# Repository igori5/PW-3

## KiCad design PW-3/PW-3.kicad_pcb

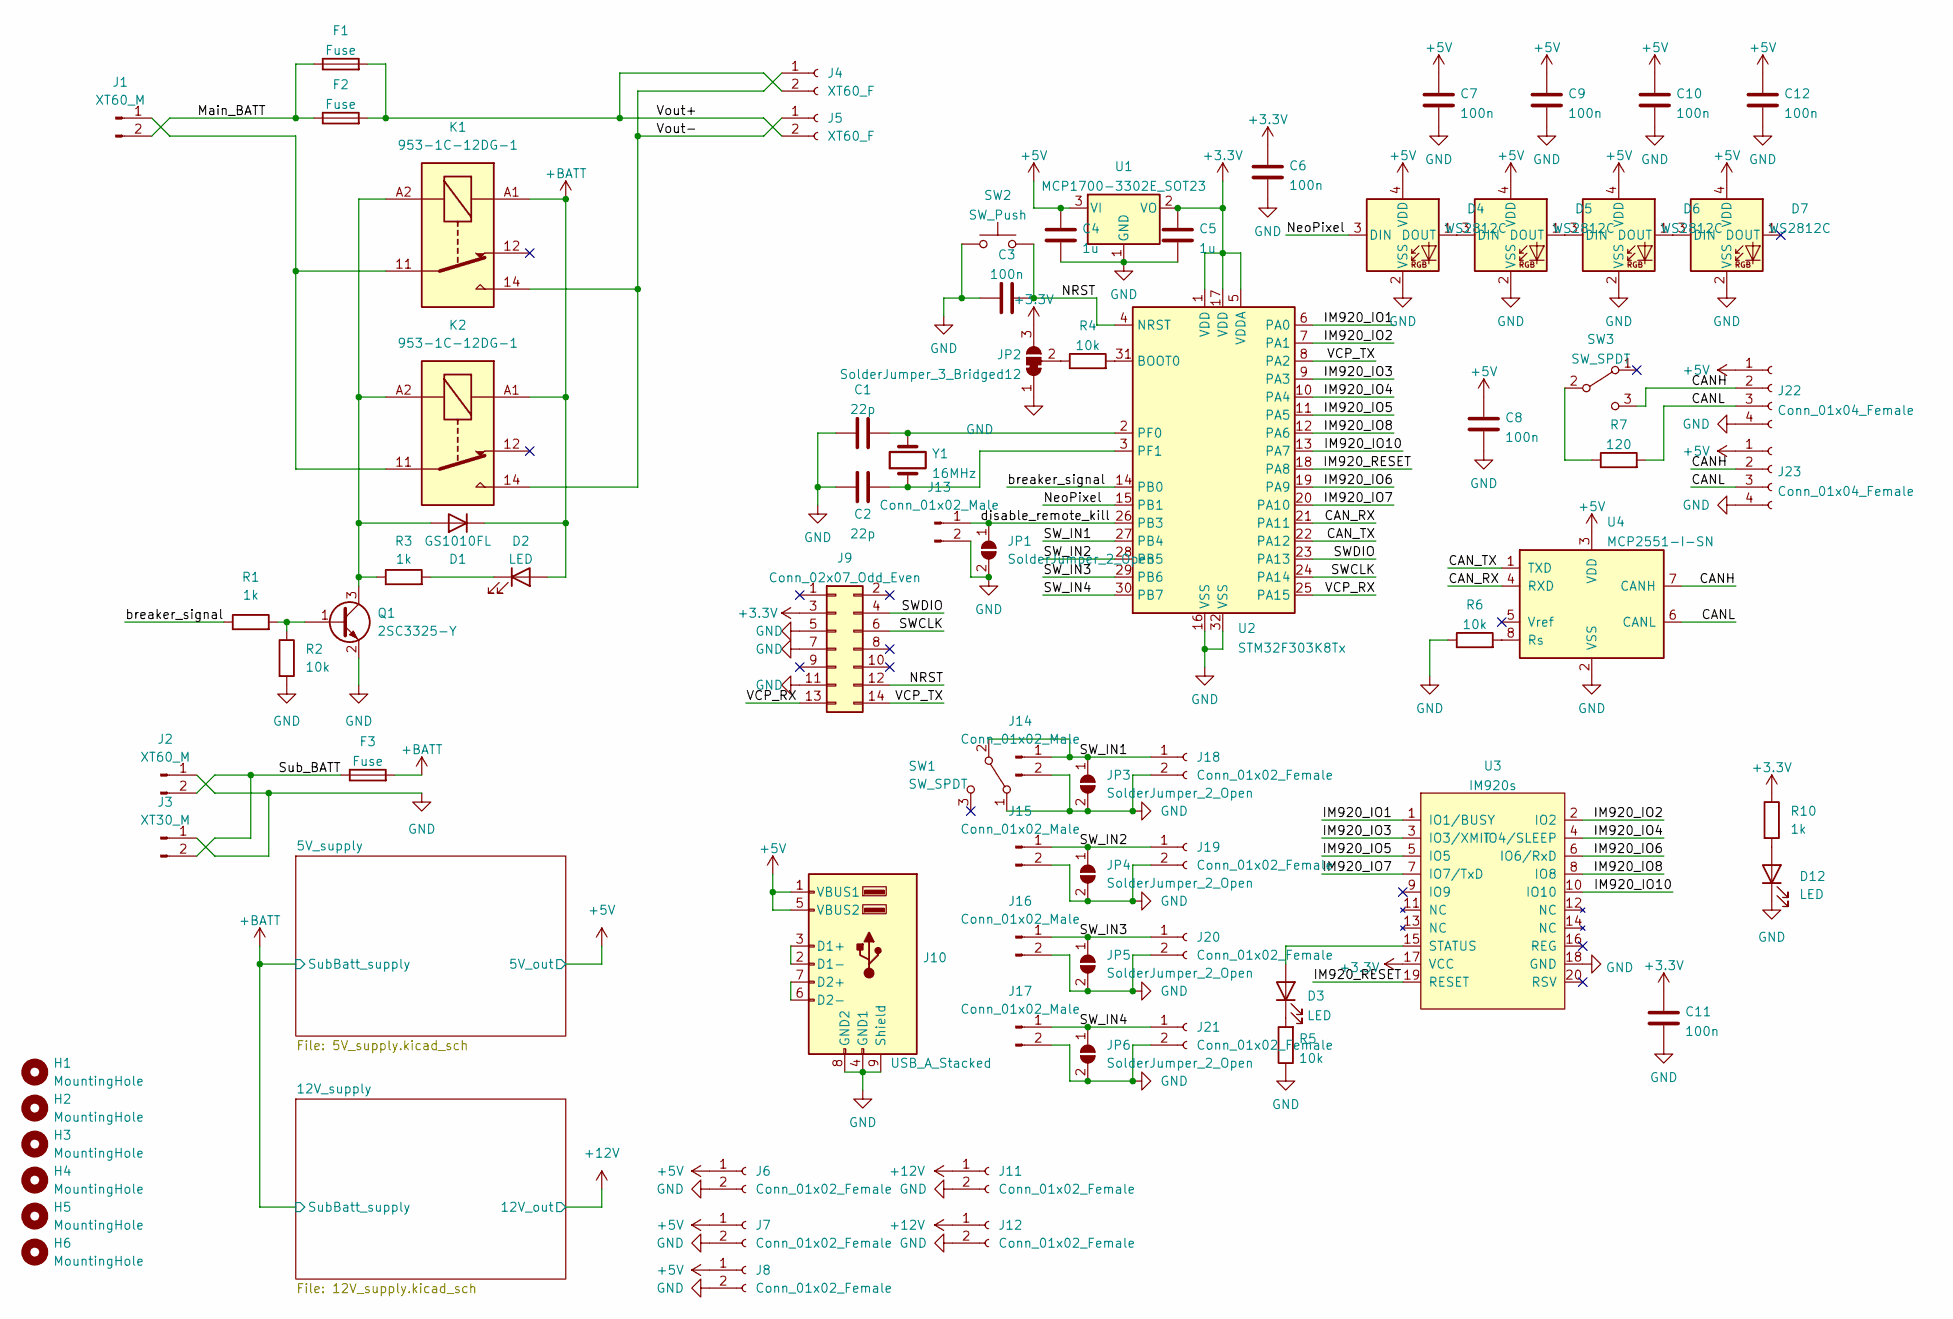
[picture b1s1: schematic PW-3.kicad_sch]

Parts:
C1, C2: 22p; C_0603_1608Metric
C3, C6, C7, C8, C9, C10, C11, C12: 100n; C_0603_1608Metric
C4, C5: 1u; C_0603_1608Metric
D1: GS1010FL; D_SOD-123
D2, D3, D12: LED; LED_0603_1608Metric
D4, D5, D6, D7: WS2812C; LED_2020Metric_WS2812C_2.0x2.0mm_P1.0mm
F1, F2, F3: Fuse; Fuseholder_Keystone_3568
H1, H2, H3, H4, H5, H6: MountingHole; MountingHole_3.2mm_M3_Pad_Via
J1, J2: XT60_M; AMASS_XT60PW-M_1x02_P7.20mm_Horizontal
J3: XT30_M; AMASS_XT30PW-M_1x02_P2.50mm_Horizontal
J4, J5: XT60_F; AMASS_XT60PW-F_1x02_P7.20mm_Horizontal
J6, J7, J8, J11, J12, J18, J19, J20, J21: Conn_01x02_Female; JST_XA_S02B-XASK-1_1x02_P2.50mm_Horizontal
J9: Conn_02x07_Odd_Even; PinHeader_2x07_P1.27mm_Vertical_SMD
J10: USB_A_Stacked; USB_A_Wuerth_61400826021_Horizontal_Stacked
J13, J14, J15, J16, J17: Conn_01x02_Male; PinHeader_1x02_P2.54mm_Vertical
J22, J23: Conn_01x04_Female; JST_XA_S04B-XASK-1_1x04_P2.50mm_Horizontal
JP1, JP3, JP4, JP5, JP6: SolderJumper_2_Open; SolderJumper-2_P1.3mm_Open_RoundedPad1.0x1.5mm
JP2: SolderJumper_3_Bridged12; SolderJumper-3_P1.3mm_Bridged12_RoundedPad1.0x1.5mm
K1, K2: 953-1C-12DG-1; Relay_SPDT_RAYEX-L90S
Q1: 2SC3325-Y; SOT-23
R1, R3, R10: 1k; R_0603_1608Metric
R2, R4, R5, R6: 10k; R_0603_1608Metric
R7: 120; R_0603_1608Metric
SW1, SW3: SW_SPDT; PinHeader_1x03_P2.54mm_Vertical
SW2: SW_Push; TVAF06-A020B-R
U1: MCP1700-3302E_SOT23; SOT-23
U2: STM32F303K8Tx; LQFP-32_7x7mm_P0.8mm
U3: IM920s
U4: MCP2551-I-SN; SOIC-8_3.9x4.9mm_P1.27mm
Y1: 16MHz; Crystal_SMD_HC49-SD

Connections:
+3V3: C5.2, C6.2, C11.2, J9.3, JP2.3 (B), R10.1, U1.2 (VO), U2.1 (VDD), U2.5 (VDDA), U2.17 (VDD), U3.17 (VCC)
+5V: C4.2, C7.2, C8.2, C9.2, C10.2, C12.2, D4.4 (VDD), D5.4 (VDD), D6.4 (VDD), D7.4 (VDD), J6.1, J7.1, J8.1, J10.1 (VBUS1), J10.5 (VBUS2), J22.1, J23.1, U1.3 (VI), U4.3 (VDD); also elsewhere on the board
+12V: J11.1, J12.1; also elsewhere on the board
+BATT: D1.1 (K), D2.2 (A), F3.2, K1.A1, K2.A1; also elsewhere on the board
/CANH: J22.2, J23.2, SW3.3 (C), U4.7 (CANH)
/CANL: J22.3, J23.3, R7.2, U4.6 (CANL)
/CAN_RX: U2.21 (PA11), U4.4 (RXD)
/CAN_TX: U2.22 (PA12), U4.1 (TXD)
/IM920_IO1: U2.6 (PA0), U3.1 (IO1/BUSY)
/IM920_IO2: U2.7 (PA1), U3.2 (IO2)
/IM920_IO3: U2.9 (PA3), U3.3 (IO3/XMIT)
/IM920_IO4: U2.10 (PA4), U3.4 (IO4/SLEEP)
/IM920_IO5: U2.11 (PA5), U3.5 (IO5)
/IM920_IO6: U2.19 (PA9), U3.6 (IO6/RxD)
/IM920_IO7: U2.20 (PA10), U3.7 (IO7/TxD)
/IM920_IO8: U2.12 (PA6), U3.8 (IO8)
/IM920_IO10: U2.13 (PA7), U3.10 (IO10)
/IM920_RESET: U2.18 (PA8), U3.19 (RESET)
/Main_BATT: F1.1, F2.1, J1.2
/NRST: C3.2, J9.12, SW2.2, U2.4 (NRST)
/NeoPixel: D4.3 (DIN), U2.15 (PB1)
/SWCLK: J9.6, U2.24 (PA14)
/SWDIO: J9.4, U2.23 (PA13)
/SW_IN1: J14.1, J18.1, JP3.1 (A), SW1.2 (B), U2.27 (PB4)
/SW_IN2: J15.1, J19.1, JP4.1 (A), U2.28 (PB5)
/SW_IN3: J16.1, J20.1, JP5.1 (A), U2.29 (PB6)
/SW_IN4: J17.1, J21.1, JP6.1 (A), U2.30 (PB7)
/Sub_BATT: F3.1, J2.2, J3.2
/VCP_RX: J9.13, U2.25 (PA15)
/VCP_TX: J9.14, U2.8 (PA2)
/Vout+: F1.2, F2.2, J4.2, J5.2
/Vout-: J4.1, J5.1, K1.14, K2.14
/breaker_signal: R1.1, U2.14 (PB0)
/disable_remote_kill: J13.1, JP1.1 (A), U2.26 (PB3)
GND: C1.1, C2.1, C3.1, C4.1, C5.1, C6.1, C7.1, C8.1, C9.1, C10.1, C11.1, C12.1, D4.2 (VSS), D5.2 (VSS), D6.2 (VSS), D7.2 (VSS), D12.1 (K), J2.1, J3.1, J6.2, J7.2, J8.2, J9.5, J9.7, J9.11, J10.4 (GND1), J10.8 (GND2), J10.9 (Shield), J11.2, J12.2, J13.2, J14.2, J15.2, J16.2, J17.2, J18.2, J19.2, J20.2, J21.2, J22.4, J23.4, JP1.2 (B), JP2.1 (A), JP3.2 (B), JP4.2 (B), JP5.2 (B), JP6.2 (B), Q1.2 (E), R2.2, R5.1, R6.1, SW1.1 (A), SW2.1, U1.1 (GND), U2.16 (VSS), U2.32 (VSS), U3.18 (GND), U4.2 (VSS); also elsewhere on the board
unnamed: D1.2 (A), K1.A2, K2.A2, Q1.3 (C), R3.1
unnamed: D2.1 (K), R3.2
unnamed: D3.2 (A), U3.15 (STATUS)
unnamed: D3.1 (K), R5.2
unnamed: D4.1 (DOUT), D5.3 (DIN)
unnamed: D5.1 (DOUT), D6.3 (DIN)
unnamed: D6.1 (DOUT), D7.3 (DIN)
unnamed: D12.2 (A), R10.2
unnamed: J1.1, K1.11, K2.11
unnamed: J10.2 (D1-), J10.3 (D1+)
unnamed: J10.6 (D2-), J10.7 (D2+)
unnamed: JP2.2 (C), R4.1
unnamed: Q1.1 (B), R1.2, R2.1
unnamed: R7.1, SW3.2 (B)
unnamed: R4.2, U2.31 (BOOT0)
unnamed: C1.2, U2.2 (PF0), Y1.2
unnamed: C2.2, U2.3 (PF1), Y1.1
unnamed: R6.2, U4.8 (Rs)

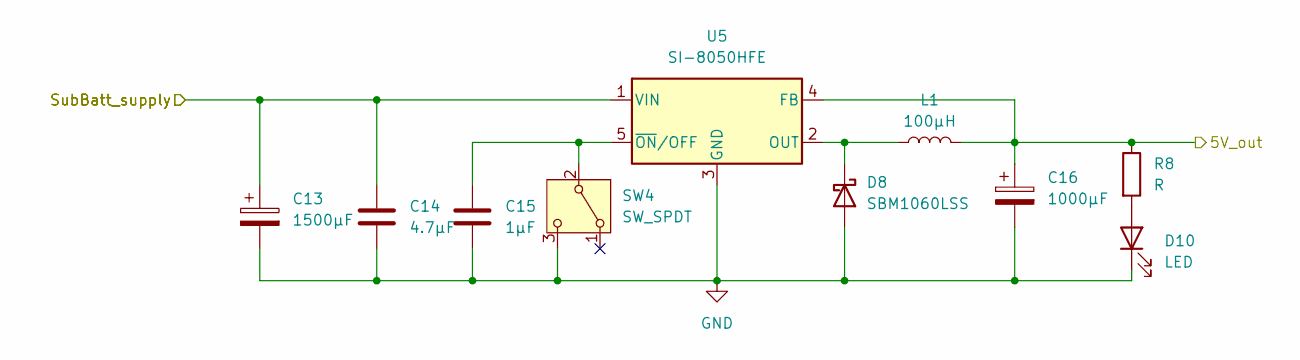
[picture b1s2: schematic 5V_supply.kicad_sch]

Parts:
C13: 1500μF; CP_Radial_D12.5mm_P5.00mm
C14: 4.7μF; C_0805_2012Metric
C15: 1μF; C_0603_1608Metric
C16: 1000μF; CP_Radial_D12.5mm_P5.00mm
D8: SBM1060LSS; D_DO-201AD_P15.24mm_Horizontal
D10: LED; LED_0603_1608Metric
L1: 100μH; L_Toroid_Vertical_L26.7mm_W14.0mm_P10.16mm_Pulse_D
R8: R; R_0603_1608Metric
SW4: SW_SPDT; PinHeader_1x03_P2.54mm_Vertical
U5: SI-8050HFE; TO-220-5_P3.4x3.7mm_StaggerOdd_Lead3.8mm_Vertical

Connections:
+5V: C16.1, L1.2, R8.1, U5.4 (FB); also elsewhere on the board
+BATT: C13.1, C14.1, U5.1 (VIN); also elsewhere on the board
GND: C13.2, C14.2, C15.2, C16.2, D8.2 (A), D10.1 (K), SW4.3 (C), U5.3 (GND); also elsewhere on the board
unnamed: D8.1 (K), L1.1, U5.2 (OUT)
unnamed: D10.2 (A), R8.2
unnamed: C15.1, SW4.2 (B), U5.5 (~ON/OFF)

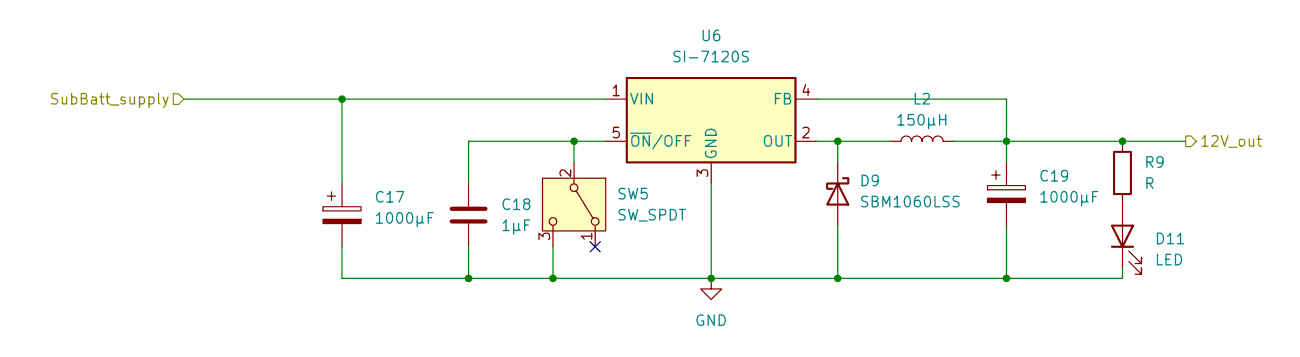
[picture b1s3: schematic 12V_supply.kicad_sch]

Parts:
C17, C19: 1000μF; CP_Radial_D12.5mm_P5.00mm
C18: 1μF; C_0603_1608Metric
D9: SBM1060LSS; D_DO-201AD_P15.24mm_Horizontal
D11: LED; LED_0603_1608Metric
L2: 150μH; L_Toroid_Vertical_L26.7mm_W14.0mm_P10.16mm_Pulse_D
R9: R; R_0603_1608Metric
SW5: SW_SPDT; PinHeader_1x03_P2.54mm_Vertical
U6: SI-7120S; TO-220-5_P3.4x3.7mm_StaggerOdd_Lead3.8mm_Vertical

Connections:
+12V: C19.1, L2.2, R9.1, U6.4 (FB); also elsewhere on the board
+BATT: C17.1, U6.1 (VIN); also elsewhere on the board
GND: C17.2, C18.2, C19.2, D9.2 (A), D11.1 (K), SW5.3 (C), U6.3 (GND); also elsewhere on the board
unnamed: D9.1 (K), L2.1, U6.2 (OUT)
unnamed: D11.2 (A), R9.2
unnamed: C18.1, SW5.2 (B), U6.5 (~ON/OFF)

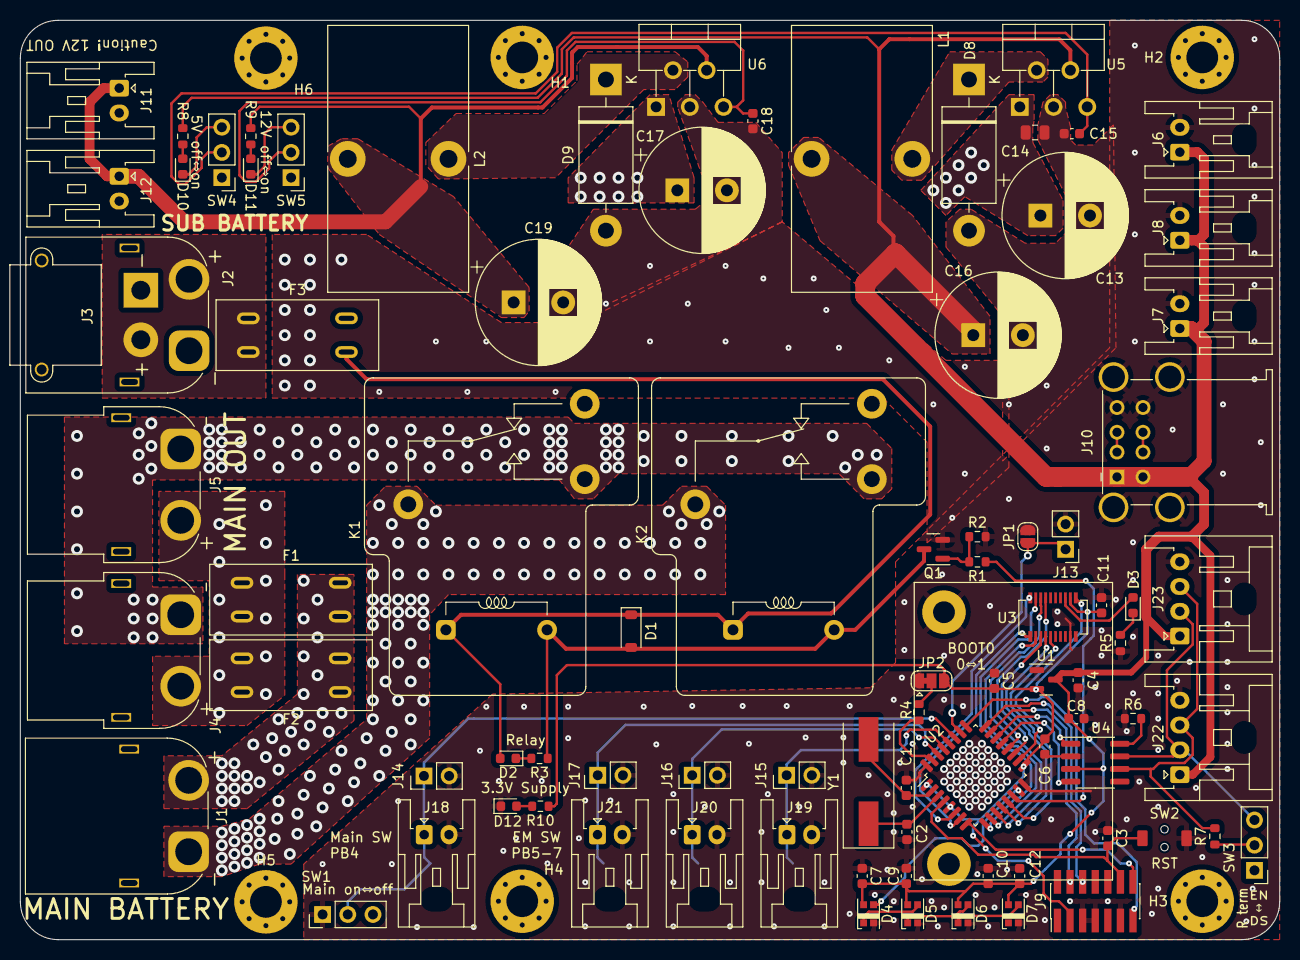
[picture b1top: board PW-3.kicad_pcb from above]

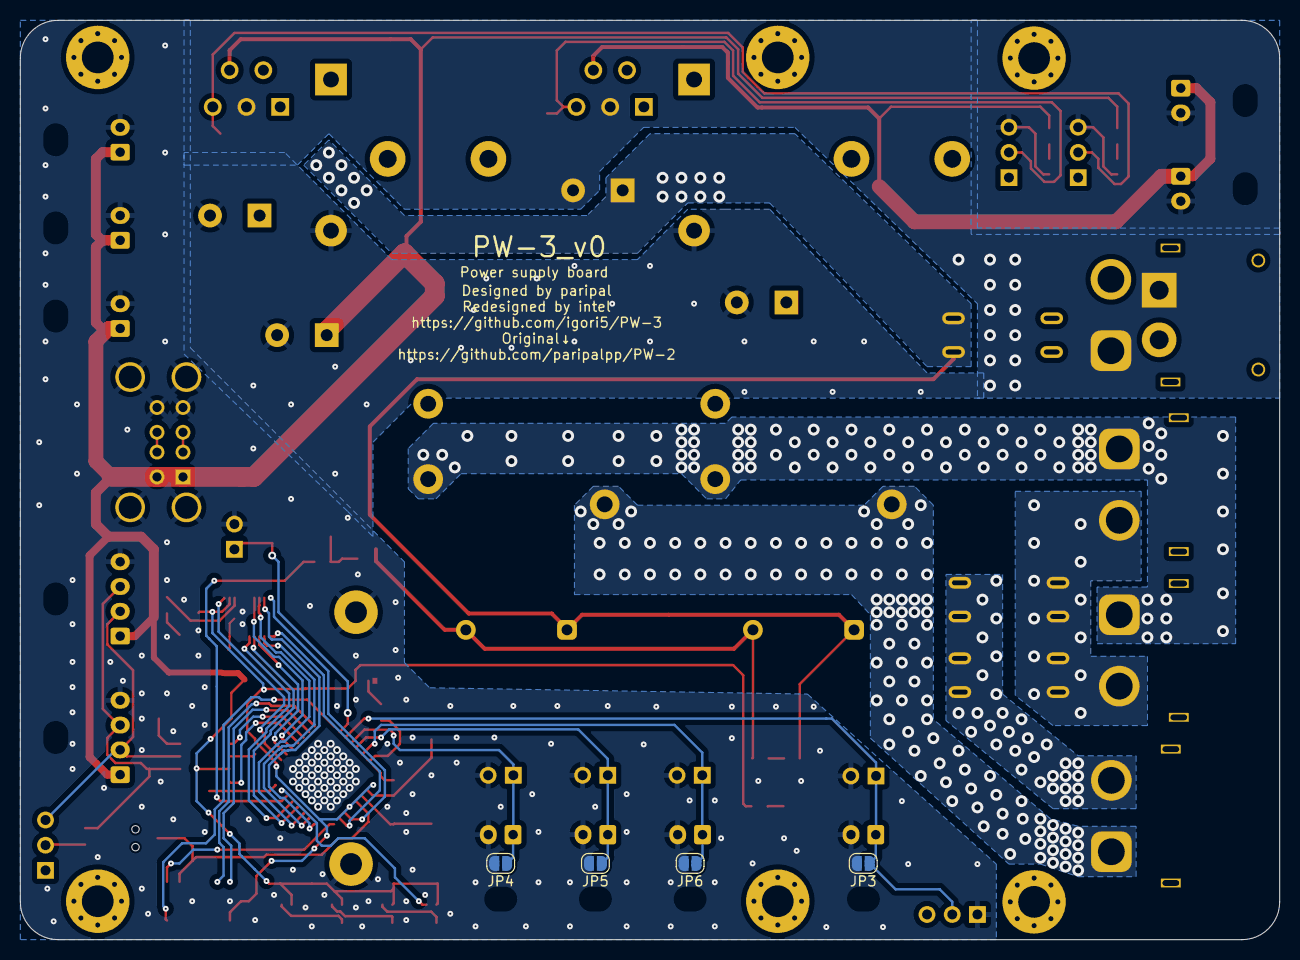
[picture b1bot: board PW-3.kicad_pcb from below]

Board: 2 copper layers, 127.0 x 92.7 mm, 96 parts (4 on the bottom side), 59 nets.
